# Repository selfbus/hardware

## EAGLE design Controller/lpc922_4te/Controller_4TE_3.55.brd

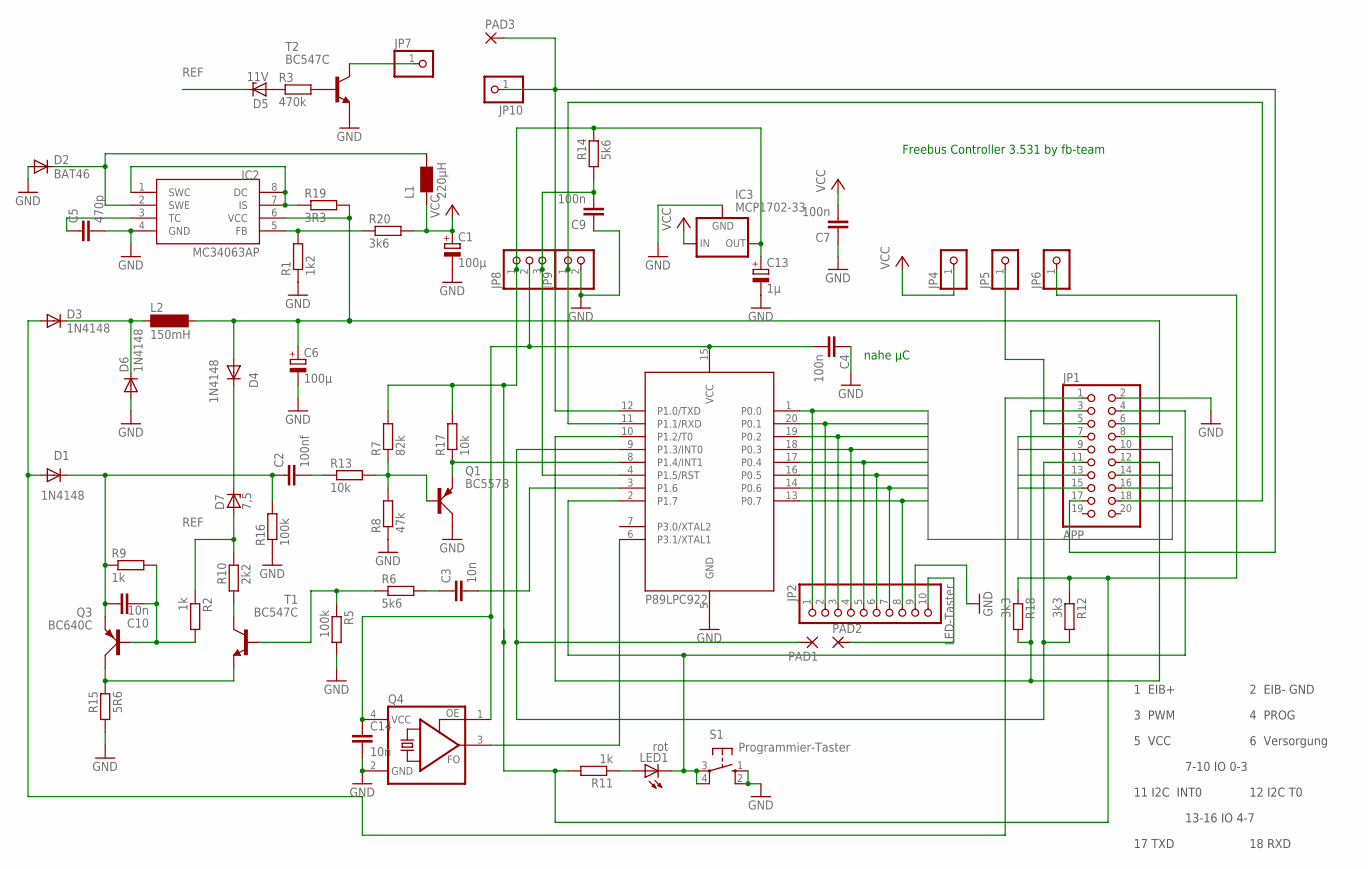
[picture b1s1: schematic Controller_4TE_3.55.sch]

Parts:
C1, C6: 100µ; E5-8,5
C2: 100nf; C050-024X044
C3, C10: 10n; C050-024X044
C4, C7, C9: 100n; C050-024X044
C5: 470p; C025-024X044
C13: 1µ; E2-4
C14: 10n; C1206
D1: 1N4148; DO35-7
D2: BAT46; C1702-05
D3, D6: 1N4148; D-2.5
D4: 1N4148; DO35-10
D5: 11V; ZDIO-10
D7: 7,5; ZDIO-7.5
IC1: 89LPC922FN; DIL20
IC2: MC34063AP; DIL08
IC3: MCP1702-33; 79LXX
JP1: APP; 2X10
JP2: LED-Taster; 1X10
JP4, JP5, JP6, JP7, JP10: PINHD-1X1; 1X01
JP8: PINHD-1X3; 1X03
JP9: PINHD-1X2; 1X02
L1: 220µH; L_RAD_D8RM5
L2: 150mH; SD12_1000
LED1: rot; LED3MM
PAD1, PAD2, PAD3: SMD2; SMD1,27-2,54
Q1: BC557B; SOT54A
Q3: BC640C; SOT54D
Q4: ASFL; ASF
R1: 1k2; 0207/10
R2, R9, R11: 1k; 0207/7
R3: 470k; 0207/7
R5: 100k; 0207/10
R6: 5k6; 0207/7
R7: 82k; 0207/7
R8: 47k; 0207/7
R10: 2k2; 0207/7
R12, R18: 3k3; 0207/10
R13, R17: 10k; 0207/7
R14: 5k6; 0207/10
R15: 5R6; 0207/10
R16: 100k; 0207/7
R19: 3R3; 0207/10
R20: 3k6; 0207/10
S1: Programmier-Taster; B3F-10XX
T1, T2: BC547C; TO92

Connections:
/RESTET: C9.2, IC1.4 (P1.5/RST), JP8.3, R14.1
DRAIN: C2.1, C10.1, D1.C, Q3.E, R9.1, R16.2
EIBIN: IC1.8 (P1.4/INT1), Q1.E, R17.1
EIB_DC: C6.+, D4.A, IC2.6 (VCC), JP1.6, L2.2, R19.2
GND: C1.-, C4.1, C5.2, C6.-, C7.1, C9.1, C13.-, C14.2, D2.A, D6.A, IC1.5 (GND), IC2.4 (GND), IC3.GND, JP1.2, JP2.9, JP9.2, Q1.C, Q4.2 (GND), R1.1, R5.2, R8.1, R15.1, R16.1, S1.1 (S), S1.2 (S1), T2.1 (E)
INT0_TASTER: IC1.9 (P1.3/INT0), JP1.11, PAD1.1, R12.2
unnamed: C3.1, R6.2
unnamed: C2.2, R13.1
unnamed: IC2.5 (FB), R1.2, R20.1
unnamed: IC2.1 (SWC), IC2.7 (IS), IC2.8 (DC), R19.1
unnamed: C3.2, IC1.3 (P1.6)
unnamed: R10.1, T1.3 (C)
unnamed: Q3.C, R15.2, T1.1 (E)
unnamed: D3.C, D6.C, L2.1
unnamed: D4.C, D7.C
unnamed: D2.C, IC2.2 (SWE), L1.1 (2)
unnamed: JP7.1, T2.3 (C)
unnamed: R5.1, R6.1, T1.2 (B)
unnamed: C5.1, IC2.3 (TC)
unnamed: Q1.B, R7.1, R8.2, R13.2
unnamed: C10.2, Q3.B, R2.2, R9.2
unnamed: D1.A, D3.A, JP1.1
unnamed: IC1.6 (P3.1/XTAL1), Q4.3 (FO)
unnamed: JP1.5, JP5.1
unnamed: R3.2, T2.2 (B)
unnamed: JP2.10, PAD2.1
unnamed: IC1.11 (P1.1/RXD), JP1.18, JP9.1
unnamed: D5.A, R3.1
unnamed: LED1.A, R11.1
P0.0: IC1.1 (P0.0), JP1.7, JP2.1
P0.1: IC1.20 (P0.1), JP1.8, JP2.2
P0.2: IC1.19 (P0.2), JP1.9, JP2.3
P0.3: IC1.18 (P0.3), JP1.10, JP2.4
P0.4: IC1.17 (P0.4), JP1.13, JP2.5
P0.5: IC1.16 (P0.5), JP1.14, JP2.6
P0.6: IC1.14 (P0.6), JP1.15, JP2.7
P0.7: IC1.13 (P0.7), JP1.16, JP2.8
PROG: IC1.2 (P1.7), JP1.4, LED1.K (C), S1.3, S1.4 (P1)
PWM: IC1.10 (P1.2/T0), JP1.3, JP1.12, R18.2
REF: D5.C, D7.A, R2.1, R10.2
TXD: IC1.12 (P1.0/TXD), JP1.17, JP10.1, PAD3.1
VCC3V3: C1.+, C7.2, IC3.IN, JP4.1, L1.2 (1), R20.2
VCC_3V3: C13.+, IC3.OUT, JP6.1, JP8.1, R7.2, R11.2, R12.1, R14.2, R17.2, R18.1
VCC_LPC: C4.2, C14.1, IC1.15 (VCC), JP8.2, Q4.1 (OE), Q4.4 (VCC)

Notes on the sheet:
Freebus Controller 3.531 by fb-team
nahe µC
P89LPC922
1 EIB+
2 EIB- GND
3 PWM
4 PROG
5 VCC
6 Versorgung
7-10 IO 0-3
11 I2C INT0
12 I2C T0
13-16 IO 4-7
17 TXD
18 RXD

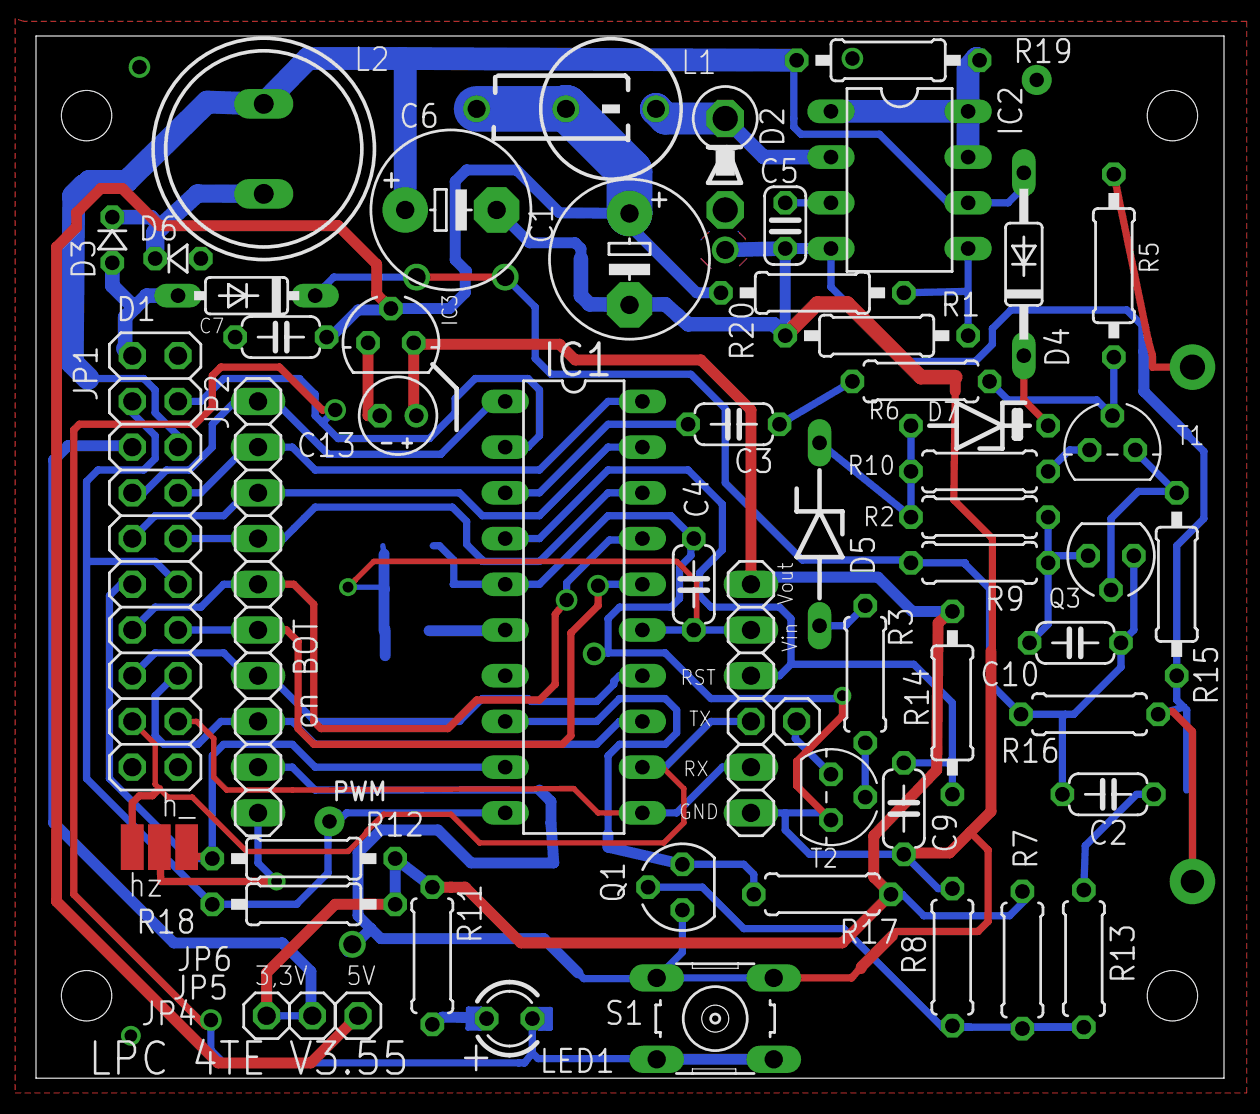
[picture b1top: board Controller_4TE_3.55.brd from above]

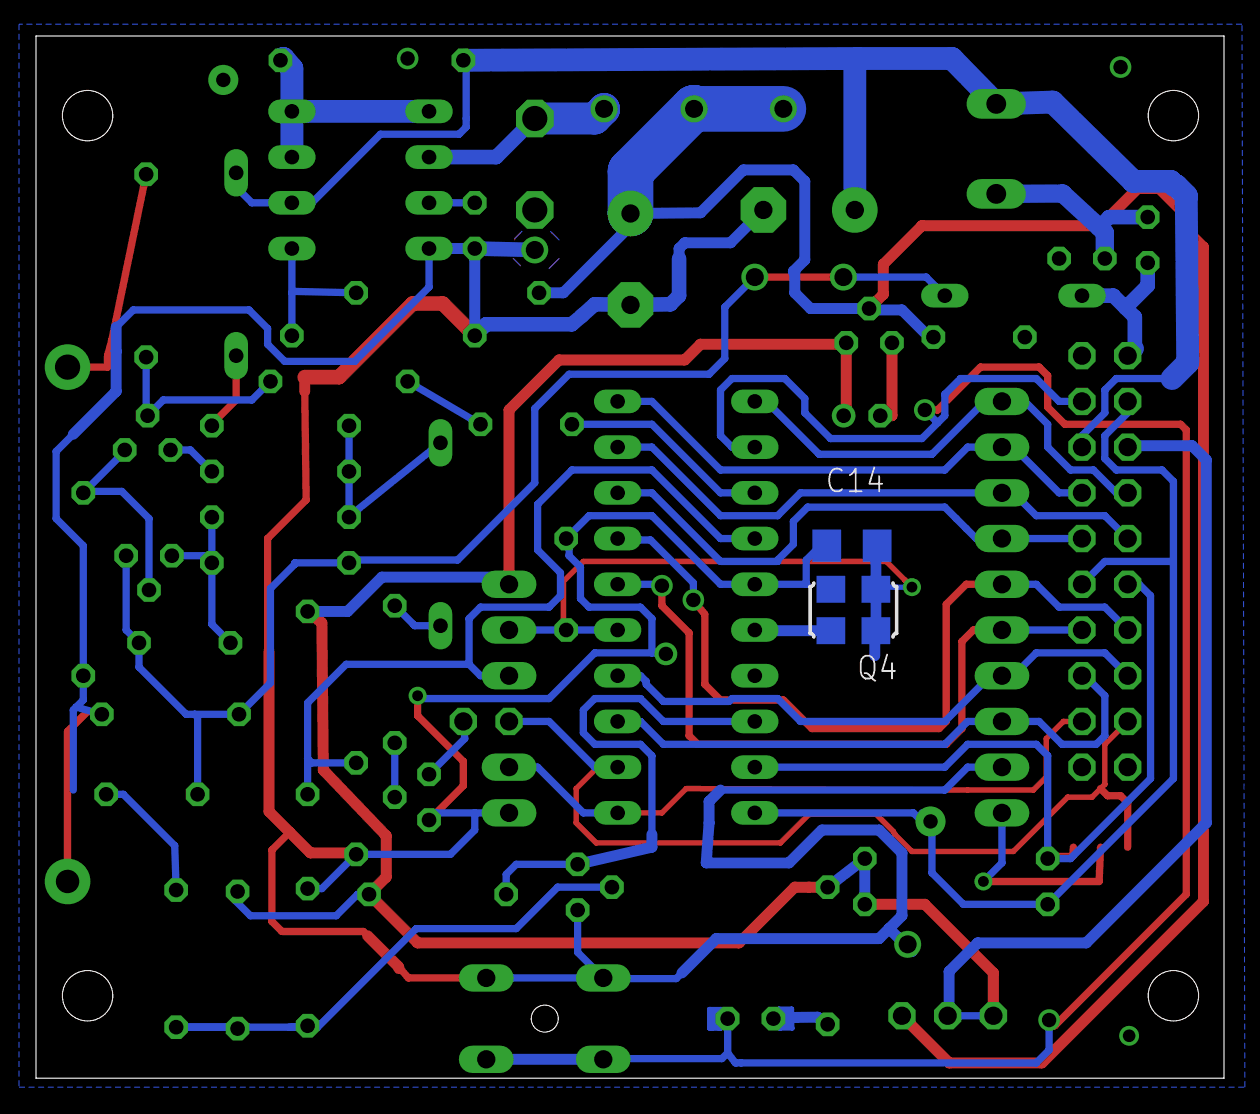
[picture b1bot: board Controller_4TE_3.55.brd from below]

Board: 2 copper layers, 66.0 x 57.9 mm, 61 parts (2 on the bottom side), 44 nets.

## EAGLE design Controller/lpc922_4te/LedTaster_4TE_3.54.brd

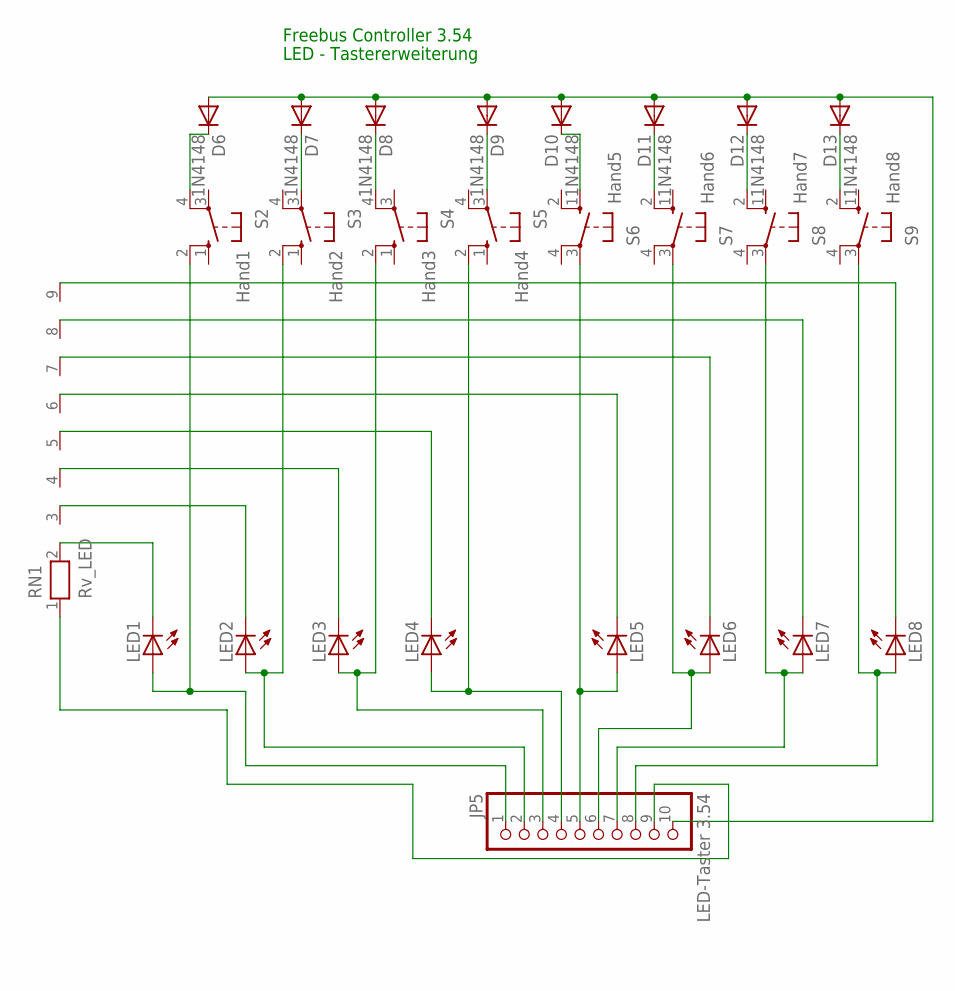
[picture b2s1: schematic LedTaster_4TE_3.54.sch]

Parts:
D6, D7, D8, D9, D10, D11, D12, D13: 1N4148; DO35-10
JP5: LED-Taster 3.54; 1X10
LED1, LED2, LED3, LED4, LED5, LED6, LED7, LED8: LED3MM
RN1: Rv_LED; RN-9
S2: Hand1; B3F-10XX
S3: Hand2; B3F-10XX
S4: Hand3; B3F-10XX
S5: Hand4; B3F-10XX
S6: Hand5; B3F-10XX
S7: Hand6; B3F-10XX
S8: Hand7; B3F-10XX
S9: Hand8; B3F-10XX

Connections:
GND: JP5.9, RN1.1
unnamed: D6.C, S2.4 (P1)
unnamed: JP5.1, LED1.A, S2.2 (S1)
unnamed: JP5.7, LED7.A, S8.3
unnamed: D10.C, S6.1 (S)
unnamed: D13.C, S9.2 (S1)
unnamed: D8.C, S4.4 (P1)
unnamed: D9.C, S5.3
unnamed: D11.C, S7.2 (S1)
unnamed: D12.C, S8.2 (S1)
unnamed: D7.C, S3.3
unnamed: JP5.5, LED5.A, S6.3
unnamed: JP5.3, LED3.A, S4.2 (S1)
unnamed: JP5.2, LED2.A, S3.2 (S1)
unnamed: JP5.6, LED6.A, S7.3
unnamed: JP5.4, LED4.A, S5.2 (S1)
unnamed: JP5.8, LED8.A, S9.3
unnamed: LED8.K (C), RN1.9
unnamed: LED1.K (C), RN1.2
unnamed: LED2.K (C), RN1.3
unnamed: LED3.K (C), RN1.4
unnamed: LED4.K (C), RN1.5
unnamed: LED5.K (C), RN1.6
unnamed: LED6.K (C), RN1.7
unnamed: LED7.K (C), RN1.8
T_MUX: D6.A, D7.A, D8.A, D9.A, D10.A, D11.A, D12.A, D13.A, JP5.10

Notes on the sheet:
Freebus Controller 3.54
LED - Tastererweiterung

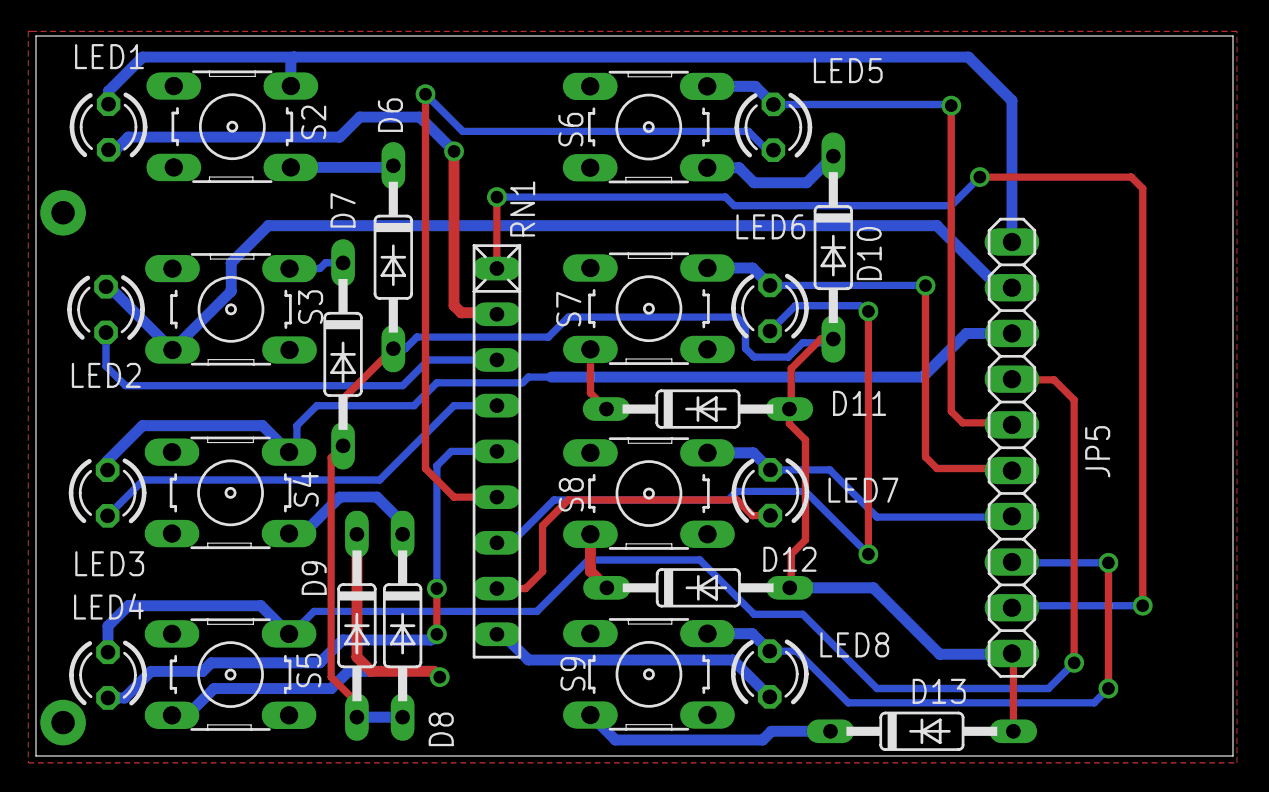
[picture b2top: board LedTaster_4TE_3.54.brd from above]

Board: 2 copper layers, 66.5 x 40.0 mm, 26 parts (0 on the bottom side), 26 nets.

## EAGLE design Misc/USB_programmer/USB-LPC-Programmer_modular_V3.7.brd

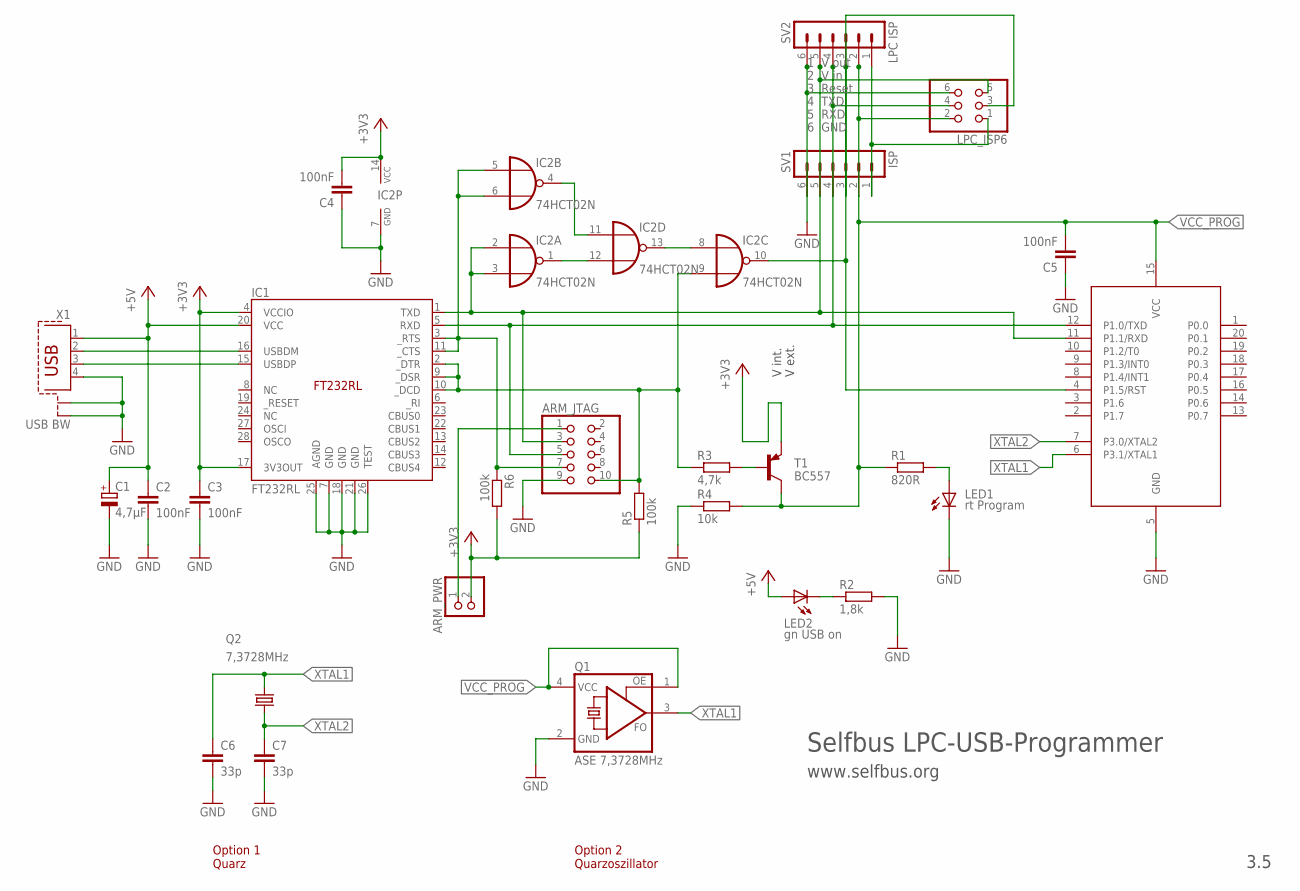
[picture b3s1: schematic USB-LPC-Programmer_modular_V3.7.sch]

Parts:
89LPC922: LPC-Sockel; DIL20
ARM_JTAG: PINHD-2X05_2.00; 2X05M
ARM_PWR: PINHD-1X02_2.54-S; 1X02-S
C1: 4,7µF; E2,5-6
C2: 100nF; C025-025X050
C3, C4, C5: 100nF; C050-024X044
C6, C7: 33p; C025-024X044
IC1: FT232RL; SSOP-28
IC2: 74HCT02N; DIL14
LED1: rt Program; LED3MM
LED2: gn USB on; LED3MM
LPC_ISP6: PINHD-2X3; 2X03
Q1: ASE 7,3728MHz; ASF
Q2: 7,3728MHz; HC49/S
R1: 820R; 0207/7
R2: 1,8k; 0207/7
R3: 4,7k; 0204/7
R4: 10k; 0207/7
R5, R6: 100k; 0207/7
SV1: ISP; MA06-1
SV2: LPC ISP; MA06-1
T1: BC557; TO92
X1: USB BW; PN61729-S

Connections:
+3V3: ARM_PWR.2, C3.1, C4.2, IC1.4 (VCCIO), IC1.17 (3V3OUT), IC2.14 (VCC), R5.1, R6.2, T1.1 (E)
+5V: C1.+, C2.1, IC1.20 (VCC), LED2.A, X1.1
GND: 89LPC922.5 (GND), ARM_JTAG.9, C1.-, C2.2, C3.2, C4.1, C5.1, C6.2, C7.2, IC1.7 (GND), IC1.18 (GND), IC1.21 (GND), IC1.25 (AGND), IC1.26 (TEST), IC2.7 (GND), LED1.K (C), LPC_ISP6.6, Q1.2 (GND), R2.2, R4.1, SV1.6, SV2.6, X1.4, X1.S1, X1.S2
unnamed: LPC_ISP6.1, SV1.1, SV2.1
unnamed: ARM_JTAG.1, ARM_PWR.1
unnamed: IC2.4 (O), IC2.11 (I0)
unnamed: 89LPC922.4 (P1.5/RST), IC2.10 (O), LPC_ISP6.3, SV1.3, SV2.3
unnamed: LED2.K (C), R2.1
unnamed: IC2.1 (O), IC2.12 (I1)
unnamed: LED1.A, R1.2
unnamed: IC1.16 (USBDM), X1.2
unnamed: IC2.8 (I0), IC2.13 (O)
unnamed: IC1.15 (USBDP), X1.3
unnamed: R3.2, T1.2 (B)
PROG_PWR_ON: ARM_JTAG.10, IC1.2 (_DTR), IC1.9 (_DSR), IC1.10 (_DCD), IC2.9 (I1), R3.1, R5.2
RTS_CTS1: ARM_JTAG.7, IC1.3 (_RTS), IC1.11 (_CTS), IC2.5 (I0), IC2.6 (I1), R6.1
USB_RX: 89LPC922.12 (P1.0/TXD), ARM_JTAG.5, IC1.5 (RXD), LPC_ISP6.4, SV1.4, SV2.4
USB_TX: 89LPC922.11 (P1.1/RXD), ARM_JTAG.3, IC1.1 (TXD), IC2.2 (I0), IC2.3 (I1), LPC_ISP6.5, SV1.5, SV2.5
VCC_PROG: 89LPC922.15 (VCC), C5.2, LPC_ISP6.2, Q1.1 (OE), Q1.4 (VCC), R1.1, R4.2, SV1.2, SV2.2, T1.3 (C)
XTAL1: 89LPC922.6 (P3.1/XTAL1), C6.1, Q1.3 (FO), Q2.2
XTAL2: 89LPC922.7 (P3.0/XTAL2), C7.1, Q2.1

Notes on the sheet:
Selfbus LPC-USB-Programmer
www.selfbus.org
3.5
2 V in
3 Reset
4 TXD
5 RXD
6 GND
1 V out
Option 1 Quarz
Option 2 Quarzoszillator
V int.
V ext.

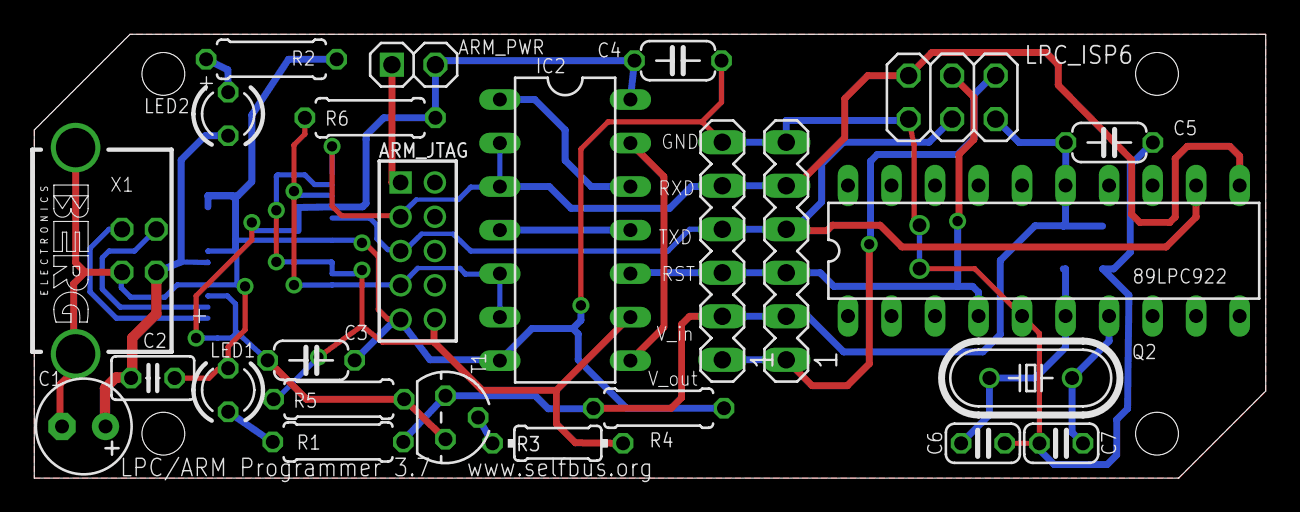
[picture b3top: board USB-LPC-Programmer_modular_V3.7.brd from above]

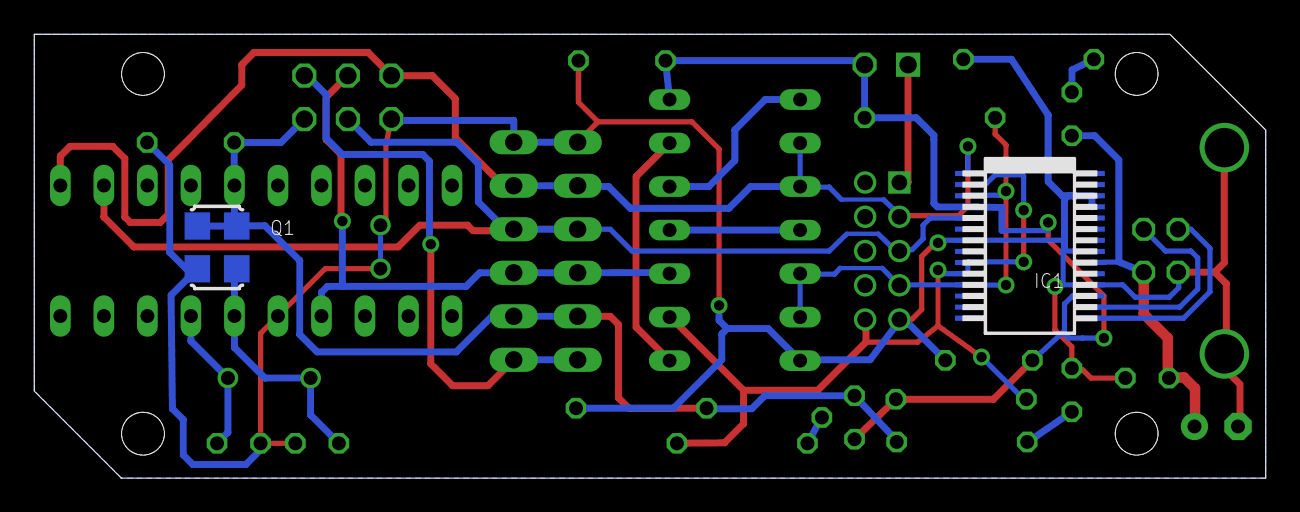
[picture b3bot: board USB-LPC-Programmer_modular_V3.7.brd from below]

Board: 2 copper layers, 71.9 x 25.9 mm, 27 parts (2 on the bottom side), 21 nets.

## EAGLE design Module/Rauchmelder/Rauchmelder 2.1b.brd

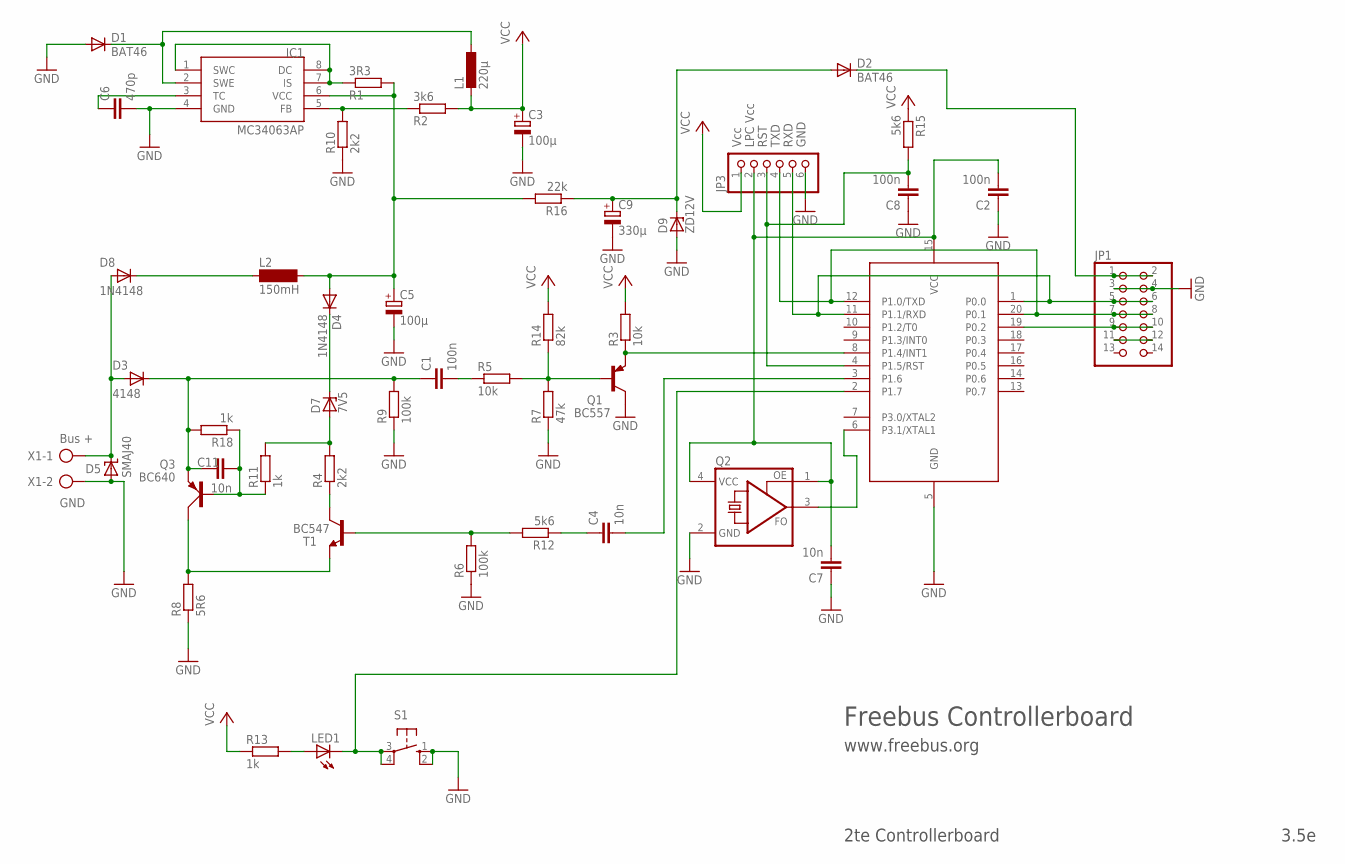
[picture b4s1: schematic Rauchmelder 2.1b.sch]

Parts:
89LPC922: 89LPC922; DIL20
C1, C2, C8: 100n; C025-024X044
C3: 100µ; E2,5-6
C4, C11: 10n; C025-024X044
C5: 100µ; E3,5-8
C6: 470p; C025-024X044
C7: 10n; C1206
C9: 330µ; E3,5-8
D1, D2: BAT46; DO34-7
D3: 4148; DO35-S
D4: 1N4148; DO35-10
D5: SMAJ40; SMBJ
D7: 7V5; ZDIO-2.5
D8: 1N4148; DO35-S
D9: ZD12V; DO34Z7
IC1: MC34063AP; DIL08
JP1: PINHD-2X7; 2X07
JP3: PINHD-1X6; 1X06
L1: 220µ; 0207/12
L2: 150mH; BS11
LED1: LED3MM
Q1: BC557; TO92
Q2: ASFL; ASF
Q3: BC640; SOT54D
R1: 3R3; 0207/7
R2: 3k6; 0207/7
R3, R5: 10k; 0207/7
R4: 2k2; 0207/2V
R6: 100k; 0207/2V
R7: 47k; 0207/7
R8: 5R6; 0207/2V
R9: 100k; 0207/7
R10: 2k2; 0207/7
R11, R18: 1k; 0207/2V
R12: 5k6; 0207/7
R13: 1k; 0207/7
R14: 82k; 0207/7
R15: 5k6; 0207/2V
R16: 22k; 0207/2V
S1: 10-XX; B3F-10XX
T1: BC547; TO92
X1: AK500/2

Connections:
EIB+: D3.P$1 (A), D5.C, D8.P$1 (A), X1.1
GND: 89LPC922.5 (GND), C2.1, C3.-, C5.-, C6.2, C7.1, C8.1, C9.-, D1.A, D5.A, D9.A, IC1.4 (GND), JP1.3, JP1.4, JP3.6, Q1.3 (C), Q2.2 (GND), R6.1, R7.1, R8.1, R9.1, R10.1, S1.1 (S), S1.2 (S1), X1.2
unnamed: 89LPC922.8 (P1.4/INT1), Q1.1 (E), R3.1
unnamed: Q1.2 (B), R5.2, R7.2, R14.1
unnamed: 89LPC922.6 (P3.1/XTAL1), Q2.3 (FO)
unnamed: C11.2, Q3.B, R11.1, R18.1
unnamed: 89LPC922.3 (P1.6), C4.2
unnamed: 89LPC922.15 (VCC), C2.2, C7.2, JP3.2, Q2.1 (OE), Q2.4 (VCC)
unnamed: 89LPC922.2 (P1.7), LED1.K (C), S1.3, S1.4 (P1)
unnamed: IC1.1 (SWC), IC1.7 (IS), IC1.8 (DC), R1.1
unnamed: LED1.A, R13.2
unnamed: C9.+, D2.A, D9.C, R16.1
unnamed: IC1.5 (FB), R2.1, R10.2
unnamed: D1.C, IC1.2 (SWE), L1.1
unnamed: D8.P$2 (B), L2.1
unnamed: C6.1, IC1.3 (TC)
unnamed: D4.C, D7.C
unnamed: C1.2, R5.1
unnamed: C5.+, D4.A, IC1.6 (VCC), L2.2, R1.2, R16.2
unnamed: D2.C, JP1.1, JP1.2
unnamed: 89LPC922.4 (P1.5/RST), C8.2, JP3.3, R15.2
unnamed: 89LPC922.19 (P0.2), JP1.9, JP1.10
unnamed: C4.1, R12.1
unnamed: R4.1, T1.3 (C)
unnamed: JP1.11, JP1.12
unnamed: D7.A, R4.2, R11.2
unnamed: Q3.C, R8.2, T1.1 (E)
unnamed: C1.1, C11.1, D3.P$2 (B), Q3.E, R9.2, R18.2
unnamed: R6.2, R12.2, T1.2 (B)
RX: 89LPC922.1 (P0.0), 89LPC922.11 (P1.1/RXD), JP1.5, JP1.6, JP3.5
TX: 89LPC922.12 (P1.0/TXD), 89LPC922.20 (P0.1), JP1.7, JP1.8, JP3.4
VCC: C3.+, JP3.1, L1.2, R2.2, R3.2, R13.1, R14.2, R15.1

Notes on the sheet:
Bus +
GND
Vcc
LPC Vcc
RST
TXD
RXD
Freebus Controllerboard
www.freebus.org
2te Controllerboard
3.5e

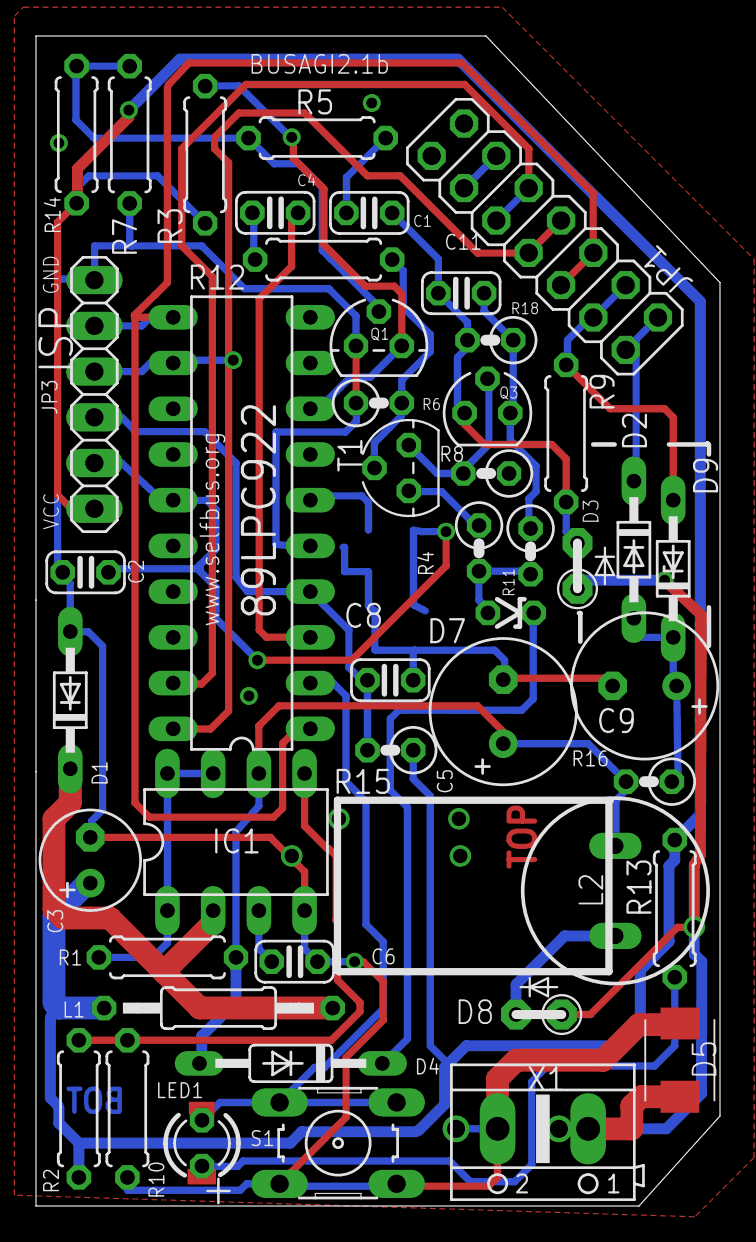
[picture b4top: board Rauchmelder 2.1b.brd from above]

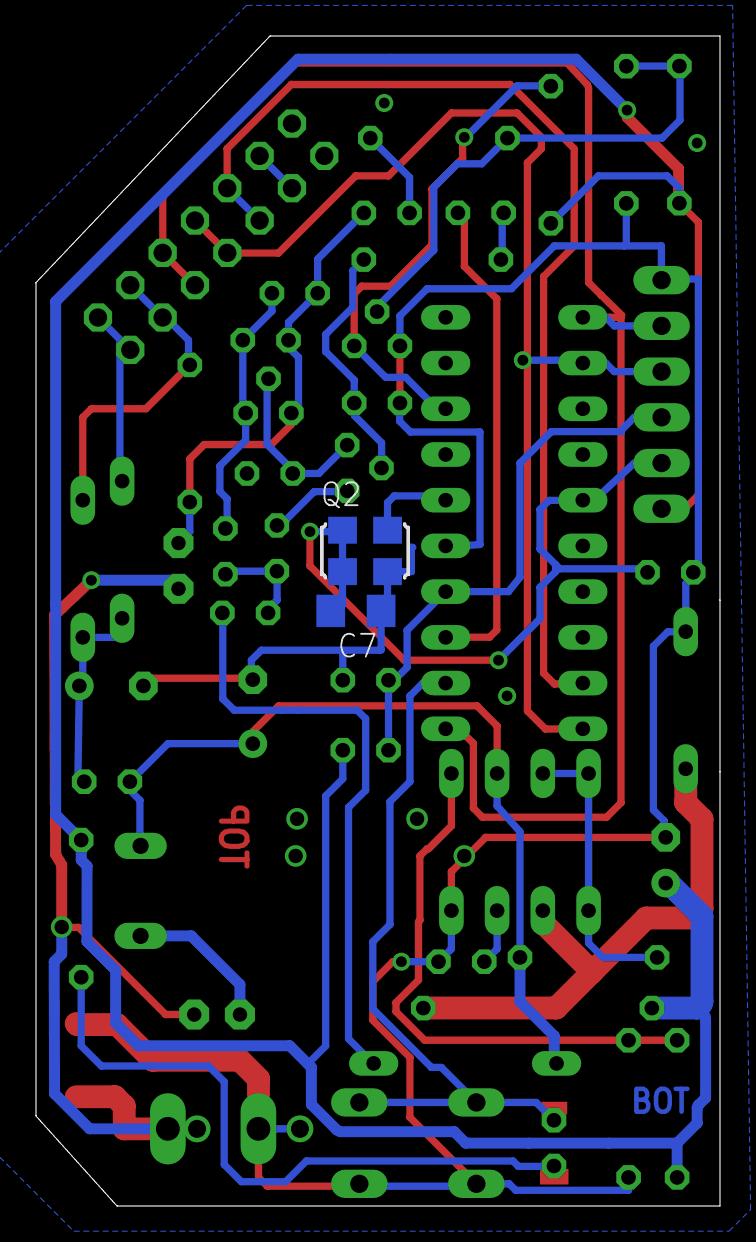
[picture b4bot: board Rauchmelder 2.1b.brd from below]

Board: 2 copper layers, 38.0 x 65.0 mm, 48 parts (2 on the bottom side), 32 nets.
